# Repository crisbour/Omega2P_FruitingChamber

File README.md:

# Omega2P_FruitingChamber
Code for Omega2+ to control humidity, temperature, air flow and lights for an automated fruiting chamber to grow mushrooms.

Sensors:
- 2x D18B20 Temperature 1-Wire
- GY-BME280  Humidity + Temperature I<sup>2</sup>C

Humidifier:
- Mist Maker 24V
- 2x Pressure Optimized Arctic fans in series to double pressure

Output inside FC:
- 2x 10W LED 6000K Lamps
- 5v Fan to homogenize temperature and humidity withi the FC

User Interface:
- 16x2 LCD display with I<sup>2</sup>C interface
- Rotary Encoder + RGB LED with I<sup>2</sup>C interface

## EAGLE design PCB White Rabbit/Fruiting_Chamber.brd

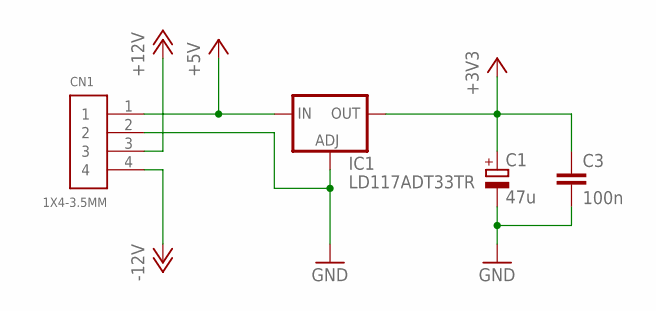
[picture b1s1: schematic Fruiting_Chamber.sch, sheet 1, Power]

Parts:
C1: 47u; E2,5-6
C3: 100n; C0603
CN1: 1X4-3.5MM; 1X04-3.5MM
IC1: LD117ADT33TR; DPACK

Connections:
+3V3: C1.+, C3.1, IC1.4 (OUT); also elsewhere on the board
+5V: CN1.1, IC1.3 (IN); also elsewhere on the board
+12V: CN1.3; also elsewhere on the board
-12V: CN1.4; also elsewhere on the board
GND: C1.-, C3.2, CN1.2, IC1.1 (ADJ); also elsewhere on the board

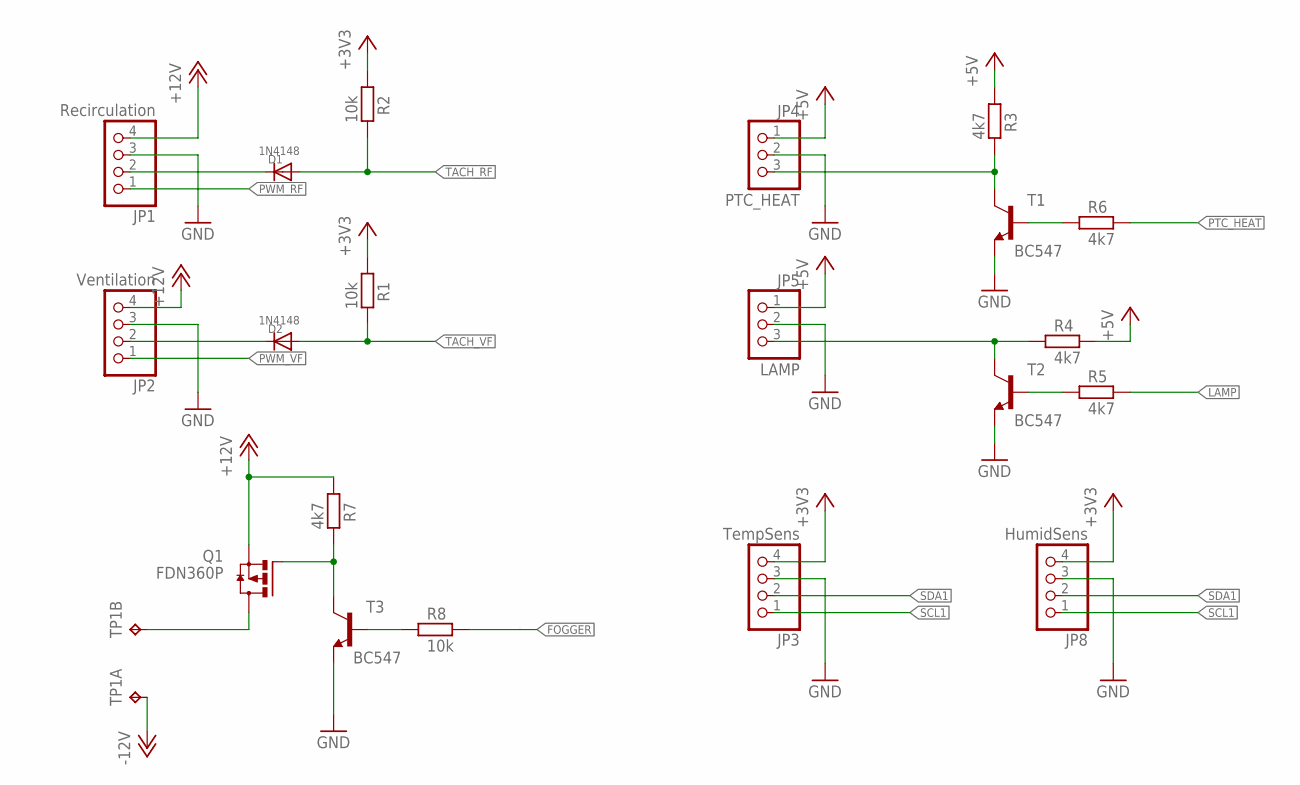
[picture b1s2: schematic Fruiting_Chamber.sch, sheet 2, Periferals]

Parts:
D1, D2: 1N4148; DO-1N4148
JP1: Recirculation; 1X04/90
JP2: Ventilation; 1X04/90
JP3: TempSens; 1X04/90
JP4: PTC_HEAT; 1X03/90
JP5: LAMP; 1X03/90
JP8: HumidSens; 1X04/90
Q1: FDN360P; SUPER-SOT3
R1, R2, R8: 10k; R0805
R3, R4, R5, R6, R7: 4k7; R0805
T1, T2, T3: BC547; TO92
TP1: TP2P2-38-20; P2-38-20

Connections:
+3V3: JP3.4, JP8.4, R1.1, R2.1; also elsewhere on the board
+5V: JP4.1, JP5.1, R3.1, R4.2; also elsewhere on the board
+12V: JP1.4, JP2.4, Q1.2 (S), R7.1; also elsewhere on the board
-12V: TP1.TP-1; also elsewhere on the board
FOGGER: R8.2; also elsewhere on the board
GND: JP1.3, JP2.3, JP3.3, JP4.2, JP5.2, JP8.3, T1.1 (E), T2.1 (E), T3.1 (E); also elsewhere on the board
LAMP: R5.2; also elsewhere on the board
unnamed: D1.C, JP1.2
unnamed: JP5.3, R4.1, T2.3 (C)
unnamed: D2.C, JP2.2
unnamed: JP4.3, R3.2, T1.3 (C)
unnamed: R6.1, T1.2 (B)
unnamed: R5.1, T2.2 (B)
unnamed: Q1.3 (D), TP1.TP-2
unnamed: Q1.1 (G), R7.2, T3.3 (C)
unnamed: R8.1, T3.2 (B)
PTC_HEAT: R6.2; also elsewhere on the board
PWM_RF: JP1.1; also elsewhere on the board
PWM_VF: JP2.1; also elsewhere on the board
SCL1: JP3.1, JP8.1; also elsewhere on the board
SDA1: JP3.2, JP8.2; also elsewhere on the board
TACH_RF: D1.A, R2.2; also elsewhere on the board
TACH_VF: D2.A, R1.2; also elsewhere on the board

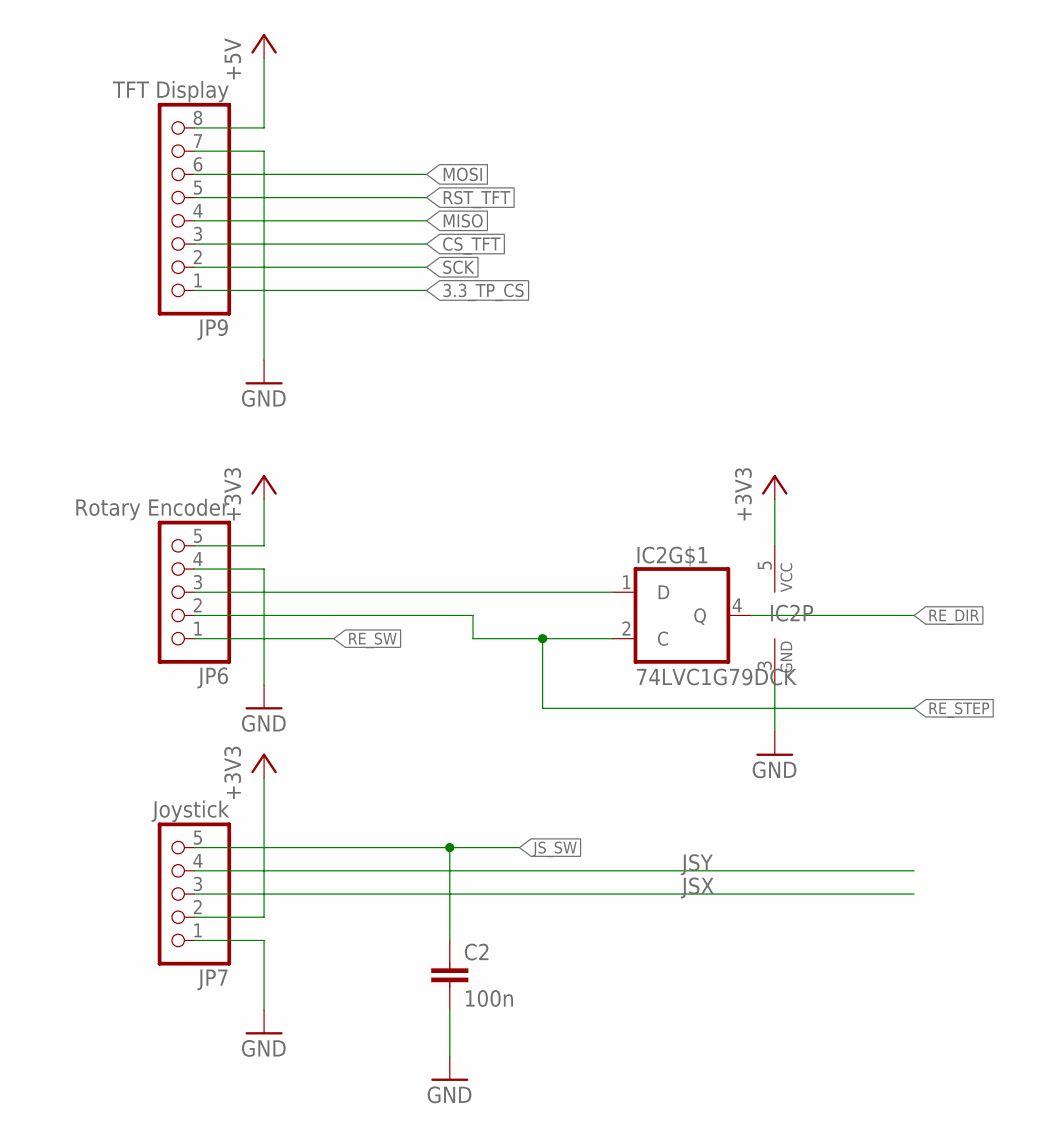
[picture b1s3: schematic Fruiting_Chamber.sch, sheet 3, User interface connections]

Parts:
C2: 100n; C0603
IC2: 74LVC1G79DCK; SC70-5
JP6: Rotary Encoder; 1X05/90
JP7: Joystick; 1X05/90
JP9: TFT Display; 1X08/90

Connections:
3.3_TP_CS: JP9.1; also elsewhere on the board
+3V3: IC2.5 (VCC), JP6.5, JP7.2; also elsewhere on the board
+5V: JP9.8; also elsewhere on the board
CS_TFT: JP9.3; also elsewhere on the board
GND: C2.2, IC2.3 (GND), JP6.4, JP7.1, JP9.7; also elsewhere on the board
JSX: JP7.3
JSY: JP7.4
JS_SW: C2.1, JP7.5
MISO: JP9.4; also elsewhere on the board
MOSI: JP9.6; also elsewhere on the board
unnamed: IC2.1 (D), JP6.3
RE_DIR: IC2.4 (Q); also elsewhere on the board
RE_STEP: IC2.2 (C), JP6.2; also elsewhere on the board
RE_SW: JP6.1; also elsewhere on the board
RST_TFT: JP9.5; also elsewhere on the board
SCK: JP9.2; also elsewhere on the board

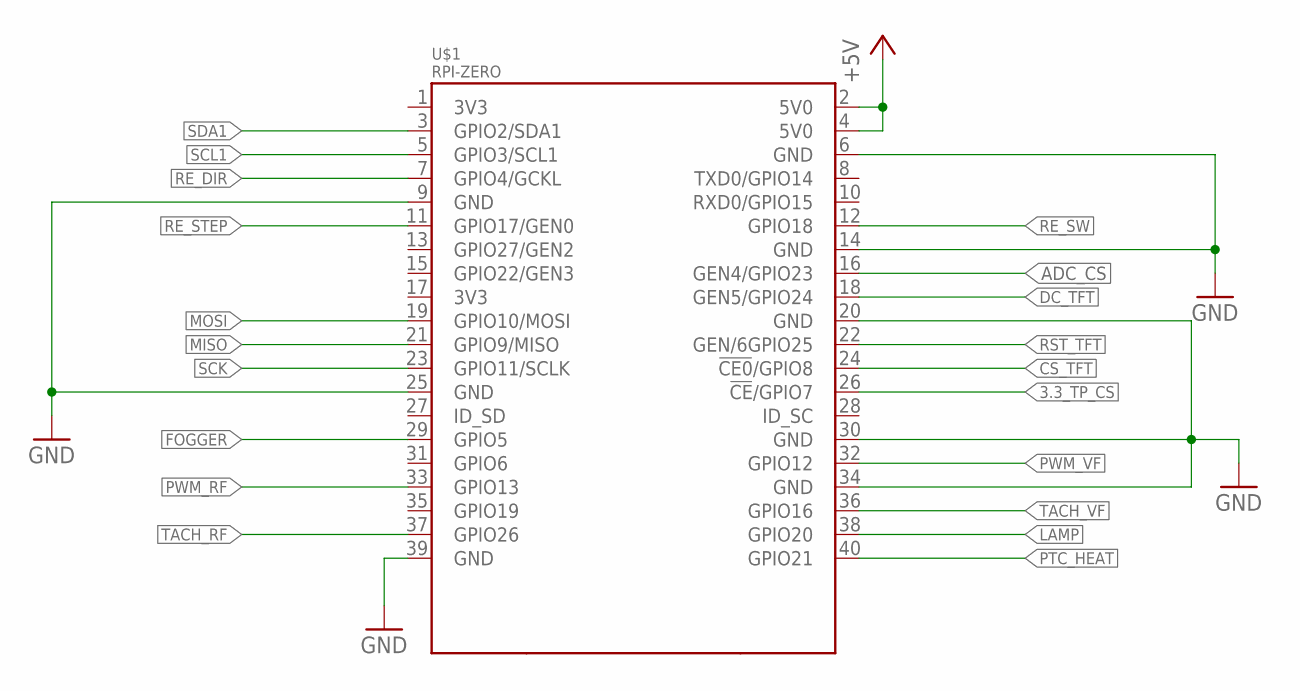
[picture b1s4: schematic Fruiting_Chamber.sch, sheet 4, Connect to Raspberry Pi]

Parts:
U$1: RPI-ZERO; RASPBERRYPI_BASTELSTUBE_V13_RASPI_BOARD_B+_FULL

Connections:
3.3_TP_CS: U$1.26 (!CE!/GPIO7); also elsewhere on the board
+5V: U$1.2 (5V0), U$1.4 (5V0); also elsewhere on the board
ADC_CS: U$1.16 (GEN4/GPIO23)
CS_TFT: U$1.24 (!CE0!/GPIO8); also elsewhere on the board
DC_TFT: U$1.18 (GEN5/GPIO24)
FOGGER: U$1.29 (GPIO5); also elsewhere on the board
GND: U$1.6 (GND), U$1.9 (GND), U$1.14 (GND), U$1.20 (GND), U$1.25 (GND), U$1.30 (GND), U$1.34 (GND), U$1.39 (GND); also elsewhere on the board
LAMP: U$1.38 (GPIO20); also elsewhere on the board
MISO: U$1.21 (GPIO9/MISO); also elsewhere on the board
MOSI: U$1.19 (GPIO10/MOSI); also elsewhere on the board
PTC_HEAT: U$1.40 (GPIO21); also elsewhere on the board
PWM_RF: U$1.33 (GPIO13); also elsewhere on the board
PWM_VF: U$1.32 (GPIO12); also elsewhere on the board
RE_DIR: U$1.7 (GPIO4/GCKL); also elsewhere on the board
RE_STEP: U$1.11 (GPIO17/GEN0); also elsewhere on the board
RE_SW: U$1.12 (GPIO18); also elsewhere on the board
RST_TFT: U$1.22 (GEN/6GPIO25); also elsewhere on the board
SCK: U$1.23 (GPIO11/SCLK); also elsewhere on the board
SCL1: U$1.5 (GPIO3/SCL1); also elsewhere on the board
SDA1: U$1.3 (GPIO2/SDA1); also elsewhere on the board
TACH_RF: U$1.37 (GPIO26); also elsewhere on the board
TACH_VF: U$1.36 (GPIO16); also elsewhere on the board

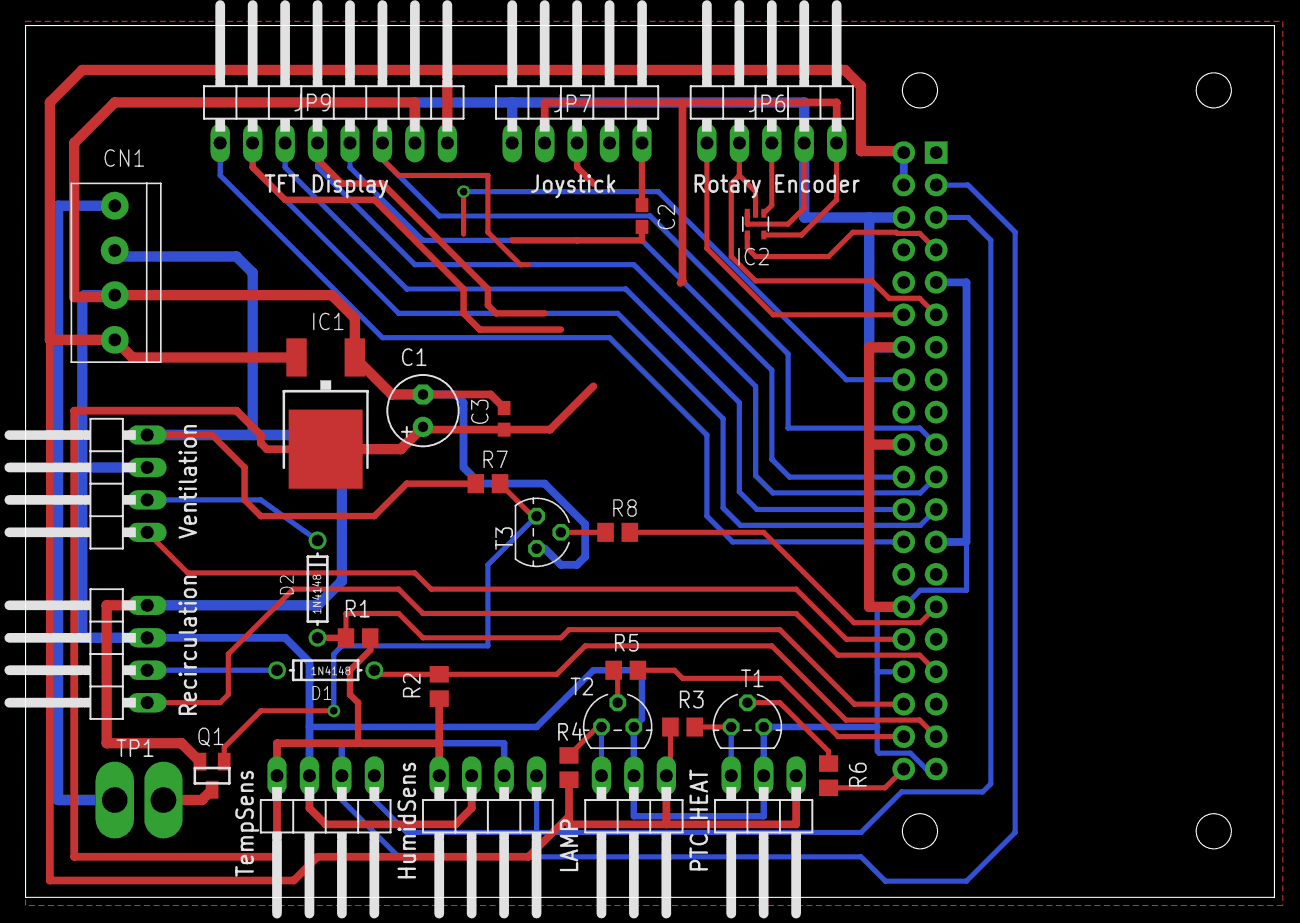
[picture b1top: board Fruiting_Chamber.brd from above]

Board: 2 copper layers, 97.8 x 68.2 mm, 31 parts (1 on the bottom side), 34 nets.

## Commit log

2020-02-06 Starting to write the code
2020-02-07 basic control
2020-02-07 basic
2020-02-07 -Every 8/16h toggle light -Every 1h humidify for 2 min
2020-02-07 Intro
    Layout
2020-02-07 Intro
    Layout (Correction)
2020-02-08 1-Wire
2020-02-08 datetime trigger
2020-02-08 Print transition between day and night
2020-02-08 PCB folder
2020-02-08 Eagle files of White Rabbit
2020-02-08 3D model of White Rabbit PCB
2020-02-08 Dependencies added
2020-02-08 changed night time
2020-02-10 Instruct only once
2020-02-18 New OS Back-up
2020-02-18 PDF schematic
2020-02-19 1k ohm resistors on transistors base
